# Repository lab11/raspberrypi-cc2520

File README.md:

raspberrypi-cc2520
==================

Code, hardware, and instructions to use the TI CC2520 with the Raspberry Pi.

[

](https://raw.github.com/bradjc/raspberrypi-cc2520/master/media/rpi-cc2520_2ndgen.jpg)

The CC2520 is a 802.15.4 (Zigbee) radio commonly used in low power wireless
sensor networks. Typically 802.15.4 radios are used with WSN motes and embedded
microcontrollers. A side-effect of being used in WSNs, however, is the
microcontrollers are very memory constrained. This is often a problem when
certain nodes need to keep data about a large network of nodes, for instance
routing information for all of the nodes. To remedy this we propose using a
Raspberry Pi as a mote in a WSN. This provides both ample storage (memory) and
convenient control as all the utilities in Linux are available.

Hardware
--------

I have a small PCB that fits directly on to the main header on the
RPi. It contains the CC2520, an SMA connector for an antenna, the DS2411
id chip, and three LEDs. The eagle files, gerbers and BOM can be found in the
`hardware/eagle/rpi-cc2520` folder.

Software
--------

### Kernel Module

In order to support the CC2520
you need the kernel module from https://github.com/ab500/linux-cc2520-driver.
This kernel module is designed to run on top of the Raspbian Linux distribution.

### Custom Version of Raspbian

Instead of compiling and installing the CC2520 kernel module yourself, you can
download a pre-configured
[image](http://nuclear.eecs.umich.edu/public/raspbian_cc2520_2013-09-18.zip)
of raspbian and put that on the sdcard instead.
Download the img and then install it to an SD
card ([here](http://elinux.org/RPi_Easy_SD_Card_Setup) is a helpful guide). For
reference, I use:

    dcfldd bs=4M if=raspbian_cc2520_2013-06-27.img of=/dev/sdd statusinterval=4

### TinyOS

All of the code I have for the RPi/CC2520 is based on TinyOS. You can use the
CC2520 driver without TinyOS (see the tests in the linux-cc2520-driver repo),
but for my purposes TinyOS was the best option.

To setup my workflow,
on your non-RPI computer you need a copy of the main TinyOS repository and the
tinyos folder from this repo. You also need to install the dependencies for
TinyOS. There are instructions here:
[http://docs.tinyos.net/tinywiki/index.php/Installing_TinyOS]. If you want
the simple Linux install I use, look here:
[http://energy.eecs.umich.edu/wiki/doku.php?id=tinyos_install]. The TinyOS
applications are designed to be cross compiled for the RPI.

In order for the TinyOS build system to figure out all the correct paths you
need to help it along a bit. Add the following to your `.bashrc` file:

    export TINYOS_ROOT_DIR=<path to git repo>/tinyos-main
    export TINYOS_ROOT_DIR_ADDITIONAL=<path to git repo>/raspberrypi-cc2520/tinyos:$TINYOS_ROOT_DIR_ADDITIONAL

You will also need the correct cross compiler for the RPi:
`arm-linux-gnueabi-gcc`. On Ubuntu:

    sudo apt-get install gcc-arm-linux-gnueabi

#### NesC

NesC is the first pass compiler for TinyOS. This compiler converts .nc files
into c code that gcc can handle. This code requires nesc version 1.3.5+.

#### Supported TinyOS Features

  - Gpio
  - Interrupts (high latency, can't use for timing critical operations)
  - 802.15.4 Packets
  - Active Message
  - Timers
  - DS2411
  - Busy wait
  - Command line arguments
  - Printf
  - Random numbers
  - Unix timestamps
  - Uart receive
  - TUN interface

Setup
-----

Once you have an RPi setup with Raspbian, there are various changes you may
need to make to the Raspbian install depending on what you want to do.

### Use IPv6
To use IPv6 you need to enable IPV6 on the RPI:

    $ sudo vim /etc/modules
    add ipv6 on a newline

### Enable Interface Forwarding

By default, Linux will not forward packets between interfaces. This
functionality is critical, however, if you want the RPi to act as a border
router for a  wireless network. Once interface forwarding is enabled, Linux
considers the machine to be a
router. This causes it to no longer receive IPv6 router advertisements, because
routers are typically statically configured. In most cases we'd rather not deal
with that, so we would like Linux to both accept router advertisements and to
forward packets.
To enable these you need to do
the following:

    sudo vim /etc/sysctl.conf
    uncomment the line: net.ipv6.conf.all.forwarding=1
    add the line: net.ipv6.conf.eth0.accept_ra=2

Usage
-----

Now to test the TinyOS code and the kernel module.

### Blink

Assuming you have the correct compilers, you should be able to run the following
on your desktop and have it compile successfully:

    cd tinyos-main/apps/Blink
    make rpi

To install it to the RPi you can simply do:

    make rpi install scp.<ipaddress of the rpi>

Then on the rpi:

    sudo ./BlinkAppC

Pins 7, 12, and 13 should be toggling and the LEDs on the interface board should
be blinking.

### RadioCountToLeds

To test the radio with TinyOS, run the RadioCountToLeds app on the RPi and
another mote. The basic process is the same as with the blink app above.

### Debug

If you need to, you can run the TinyOS application with GDB. To add the debug
symbols:

    make rpi debug

Then on the RPi:

    sudo gdb ./AppC

Setting Up an Actual Border Router
----------------------------------

These are the instructions for how I'm testing the RPI as a border router.
Because IPv6 support is anything but universal, this requires more manual setup
than desired.

My setup consists of using Hurricane Electric to tunnel IPv6 to the RPi and all
computers I wish to send packets to.

### Setting up the Tunnel

Go to http://www.tunnelbroker.net/ to setup a tunnel to the IP address of the
RPI. The Hurricane Electric instructions will setup an IPv6 in IPv4 tunnel
device on the RPi.

Hurricane Electric conveniently provides every tunnel it creates a /64 prefix
that they route to the end of the tunnel. This is perfect for the BorderRouter
application as the WSN nodes can use IP addresses in this range.

### Setting Up the Border Router

The RPi will be running the BorderRouter app.
The border router is required to determine the 64 bit IPv6 prefix that the
network uses. How this prefix is assigned can be handled in several ways:
IPv6 Neighbor Discovery, DHCP, or static configuration.

#### Addressing: IPv6 Neighbor Discovery

To use router solicitations and router advertisements to assign a prefix
for the network, set `BLIP_ADDR_AUTOCONF=1` in the Makefile, as well
as `BLIP_SEND_ROUTER_SOLICITATIONS=1`. This will cause the border router
to send a router solicitation in order to receive a router solicitation
and then use the prefix that it receives from the router advertisement as the
network prefix.

The next step is something must respond to the router solicitations. To do
this, setup [radvd](https://github.com/reubenhwk/radvd) to respond to router
solictitations on the interface that the border router creates. To configure
the name of the TUN device the border router creates, run the border router
app like this:

    sudo ./BorderRouterC -i tunname

#### Addressing: DHCP

Blip supports both static and dynamic IP addresses. If you wish to reduce your
burden when flashing nodes and use dynamic addresses, you need to be
running a DHCP server. Ideally you could use any router's DHCP server, but in
the likely case that isn't available, you can run a DHCP server on the RPI.

I'm using [Dibbler](http://klub.com.pl/dhcpv6/). I couldn't figure out how to
cross compile it so I downloaded it to the RPi and built it on there (yeah it
took a little while). Alternatively, you can try getting
[these directions](http://klub.com.pl/dhcpv6/doxygen/dc/dec/compilation.html#compilationCross)
for cross-compiling Dibbler to work.

    tar xf dibbler-x.x.x.tar.gz
    ./configure
    make
    sudo make install

Running Dibbler is pretty straightforward. The last key is the configuration file
located at `/etc/dibbler/server.conf`. Here is mine:

    log-colors true

    iface relay1 {
     relay tun0

     class {
      pool <ipv6/64 from Hurricane Electric>/64
     }
    }

    iface "tun0" {
     class {
      pool <ipv6/64 from Hurricane Electric>/64
     }

     client link-local fe80::212:6d52:5000:1 {
      address <ipv6/64 from Hurricane Electric>:1
      prefix <ipv6/64 from Hurricane Electric>/64
     }
    }

#### Addressing: Static

To assign a static prefix, uncomment `components StaticIPAddressC;` from `BorderRouterC.nc`
and update the prefix in `brconfig.ini`.

### Compile and Install

In `/tinyos/apps/BorderRouter`:
    
    make rpi install scp.<ip address of rpi>

### Operation

Once running the BorderRouter application will forward all IPv6 packets that are not destined
for a node in the network to the TUN interface, and then Linux can route those packets
to the Internet.

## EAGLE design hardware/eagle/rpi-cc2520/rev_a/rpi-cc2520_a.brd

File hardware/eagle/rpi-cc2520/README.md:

RPi - CC2520 Rev. A
===================

This PCB contains the TI CC2520 and Maxim DS2411 and fits directly on to P1
on the Raspberry Pi.

This design is known to be working.

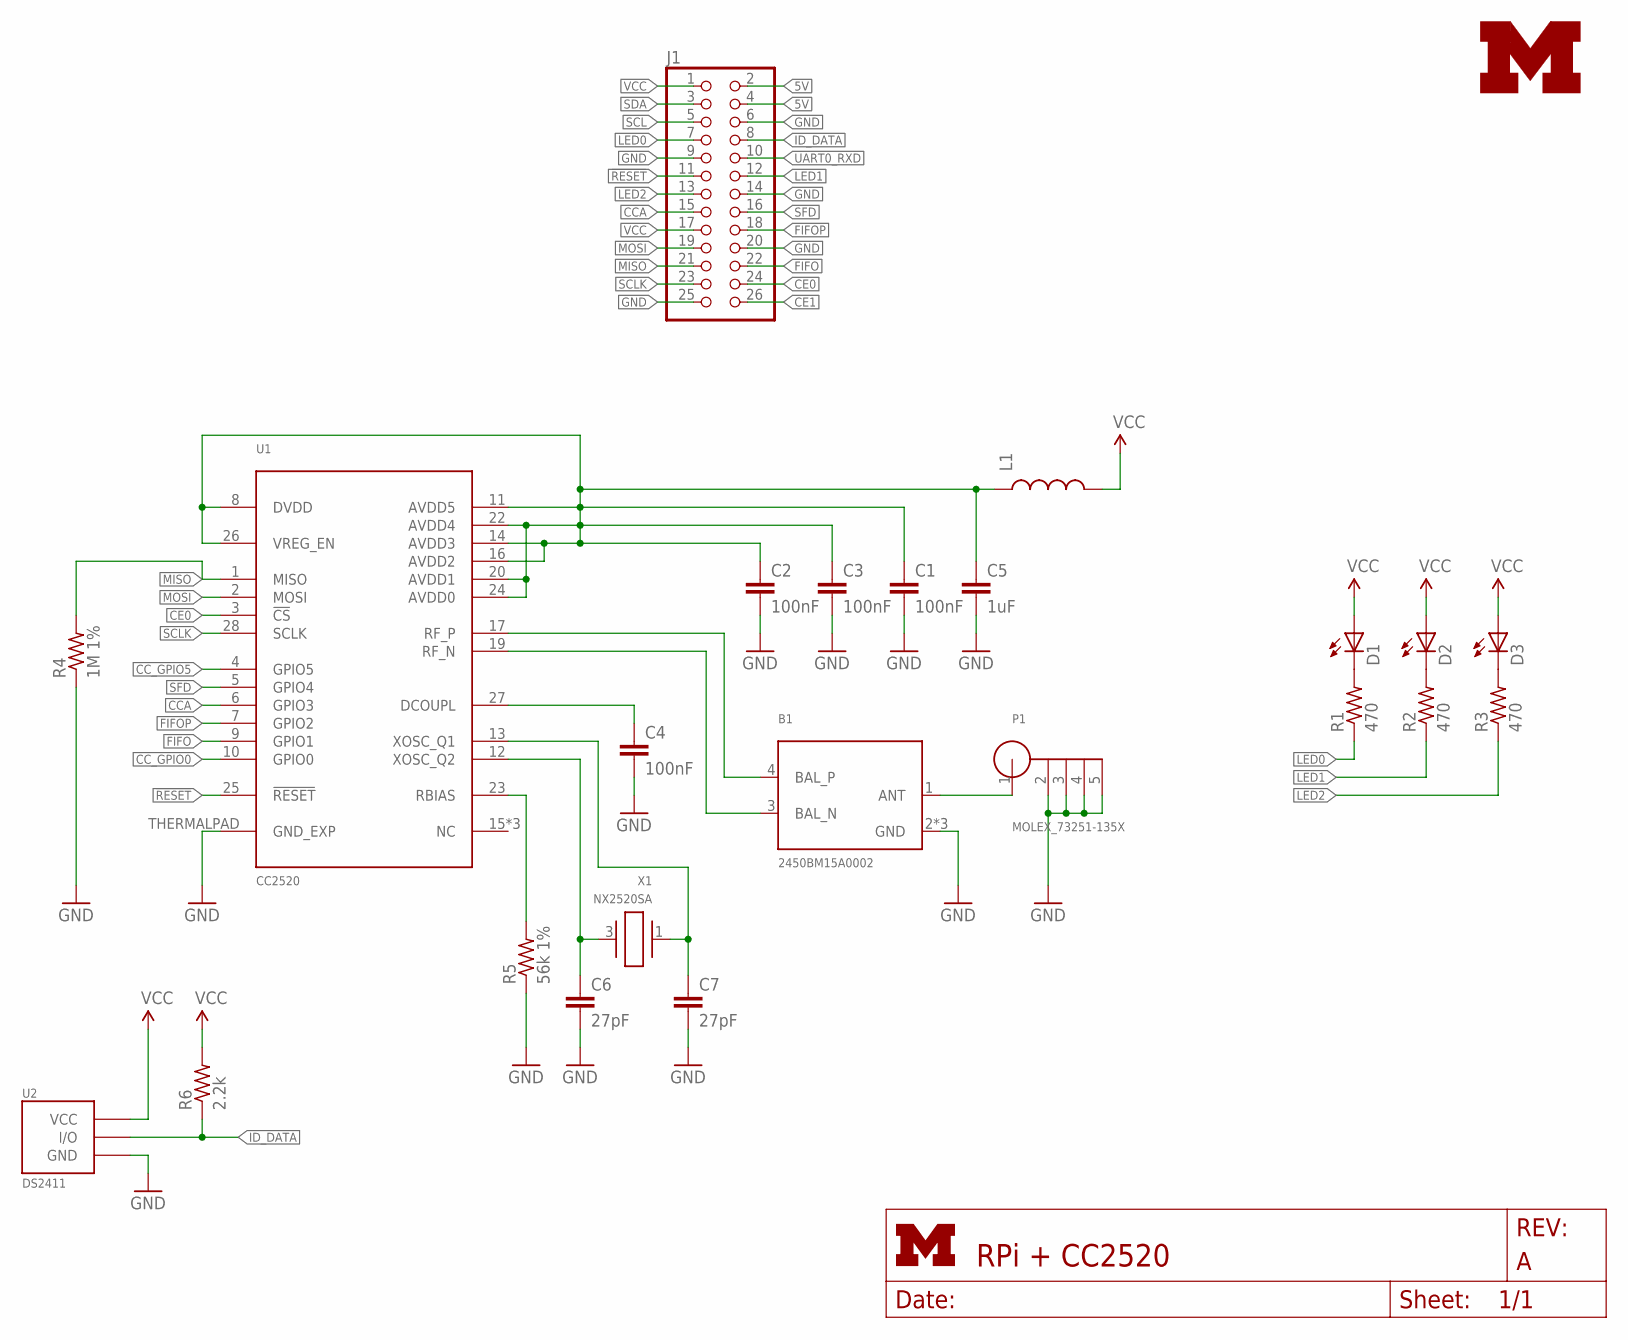
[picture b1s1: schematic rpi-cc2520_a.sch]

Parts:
B1: 2450BM15A0002; 2450BM
C1, C2, C3, C4: 100nF; C0402; DIGIKEY 490-1318-1-ND
C5: 1uF; C0603; DIGIKEY 490-1550-1-ND
C6, C7: 27pF; C0402; DIGIKEY 490-5869-1-ND
D1: LED0603; LED-0603; DIGIKEY 160-1834-1-ND
D2: LED0603; LED-0603; DIGIKEY 160-1835-1-ND
D3: LED0603; LED-0603; DIGIKEY 160-1837-1-ND
J1: PINHD-2X13; 2X13; DIGIKEY SAM1204-13-ND
L1: INDUCTOR0603; 0603; DIGIKEY 490-1015-1-ND
P1: MOLEX_73251-135X; SMA-J/PCB
R1, R2, R3: 470; R0402; DIGIKEY RHM470JCT-ND
R4: 1M 1%; R0402; DIGIKEY RHM1.00MCDCT-ND
R5: 56k 1%; R0402; DIGIKEY P56.0KLCT-ND
R6: 2.2k; R0402; DIGIKEY RHM2.2KCECT-ND
U1: CC2520; S-PVQFN-N28
U2: DS2411; SOT-23
U$1: UMICH_SOLID_SMALL; UMICH_SOLID_75MIL
X1: NX2520SA

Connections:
5V: J1.2, J1.4
!RESET: J1.11, U1.25 (!RESET)
CCA: J1.15, U1.6 (GPIO3)
CC_GPIO0: U1.10 (GPIO0)
CC_GPIO5: U1.4 (GPIO5)
CE0: J1.24, U1.3 (!CS)
CE1: J1.26
FIFO: J1.22, U1.9 (GPIO1)
FIFOP: J1.18, U1.7 (GPIO2)
GND: B1.2 (GND), B1.5 (GND), B1.6 (GND), C1.2, C2.2, C3.2, C4.2, C5.2, C6.2, C7.2, J1.6, J1.9, J1.14, J1.20, J1.25, P1.2, P1.3, P1.4, P1.5, R4.1, R5.1, U1.THERMALPAD (GND_EXP), U2.3 (GND)
ID_DATA: J1.8, R6.1, U2.1 (I/O)
LED0: J1.7, R1.1
LED1: J1.12, R2.1
LED2: J1.13, R3.1
MISO: J1.21, R4.2, U1.1 (MISO)
MOSI: J1.19, U1.2 (MOSI)
unnamed: D1.C, R1.2
unnamed: D2.C, R2.2
unnamed: D3.C, R3.2
unnamed: C1.1, C2.1, C3.1, C5.1, L1.1, U1.8 (DVDD), U1.11 (AVDD5), U1.14 (AVDD3), U1.16 (AVDD2), U1.20 (AVDD1), U1.22 (AVDD4), U1.24 (AVDD0), U1.26 (VREG_EN)
unnamed: B1.1 (ANT), P1.1
unnamed: C7.1, U1.13 (XOSC_Q1), X1.1
unnamed: C4.1, U1.27 (DCOUPL)
unnamed: C6.1, U1.12 (XOSC_Q2), X1.3 (2)
unnamed: R5.2, U1.23 (RBIAS)
RF_N: B1.3 (BAL_N), U1.19 (RF_N)
RF_P: B1.4 (BAL_P), U1.17 (RF_P)
SCL: J1.5
SCLK: J1.23, U1.28 (SCLK)
SDA: J1.3
SFD: J1.16, U1.5 (GPIO4)
UART0_RXD: J1.10
VCC: D1.A, D2.A, D3.A, J1.1, J1.17, L1.2, R6.2, U2.2 (VCC)

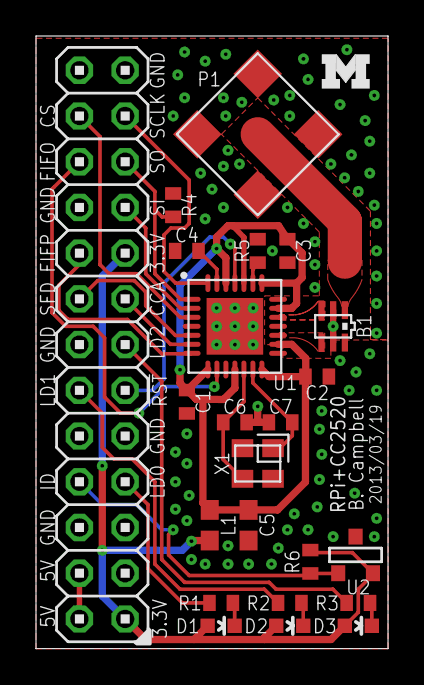
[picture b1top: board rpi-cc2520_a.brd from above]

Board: 2 copper layers, 19.6 x 34.0 mm, 24 parts (0 on the bottom side), 27 nets.

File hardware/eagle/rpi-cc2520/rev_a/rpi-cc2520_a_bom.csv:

# Bill of Materials
# Converted from rpi-cc2520_a_bom.xls
# Generated by bom_to_text.py

Qty,Value,Device,Package,Parts,Description,DIGIKEY,DIGIREEL
1,,2450BM15A0002,2450BM,B1,BALUN JTI MATCHED ZIGBEE,712-1536-1-ND,712-1536-6-ND
4,100nF,C-EUC0402,C0402,"C1, C2, C3, C4","CAPACITOR, European symbol",490-1318-1-ND,490-1318-6-ND
1,1uF,C-EUC0603,C0603,C5,"CAPACITOR, European symbol",490-1550-1-ND,490-1550-6-ND
2,27pF,C-EUC0402,C0402,"C6, C7","CAPACITOR, European symbol",490-5869-1-ND,490-5869-6-ND
1,,LED0603,LED-0603,D1,Green LED,160-1834-1-ND,160-1834-6-ND
1,,LED0603,LED-0603,D2,Red LED,160-1835-1-ND,160-1835-6-ND
1,,LED0603,LED-0603,D3,Blue LED,160-1837-1-ND,160-1837-6-ND
1,,PINHD-2X13,2X13,J1,PIN HEADER,SAM1204-13-ND,SAM1204-13-ND
1,,INDUCTOR0603,L0603,L1,Inductors,490-1015-1-ND,490-1015-6-ND
1,,MOLEX_73251-135X,SMA-J/PCB,P1,SMA JACK SMT 50 OHM,WM9357-ND,WM9357-ND
3,470,R-US_R0603,R0402,"R1, R2, R3","RESISTOR, American symbol",RHM470JCT-ND,RHM470JTR-ND
1,1M 1%,R-US_R0402,R0402,R4,"RESISTOR, American symbol",RHM1.00MCDCT-ND,RHM1.00MCDDKR-ND
1,56k 1%,R-US_R0402,R0402,R5,"RESISTOR, American symbol",P56.0KLCT-ND,P56.0KLDKR-ND
1,2.2k,R-US_R0402,R0402,R6,"RESISTOR, American symbol",RHM2.2KCECT-ND,RHM2.2KCEDKR-ND
1,,CC2520,S-PVQFN-N28,U1,2.4 GHZ IEEE 802.15.4/ZIGBEE® RF TRANSCEIVER,296-22996-1-ND,296-22996-6-ND
1,,DS2411,SOT-23,U2,IC SILICON SERIAL NUMBER SOT-23,DS2411R+CT-ND,DS2411R+DKR-ND
1,,NX2520SA,NX2520SA,X1,CRYSTAL 32MHZ 10PF SMD,644-1065-1-ND,644-1065-6-ND
1,,ANTENNA,,,ANTENNA 2.45GHZ 1/4 WAVE SMA,ANT-2.4-CW-RH-SMA-ND,ANT-2.4-CW-RH-SMA-ND

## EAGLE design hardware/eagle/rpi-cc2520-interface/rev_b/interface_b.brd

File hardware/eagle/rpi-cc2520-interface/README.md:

RPi - CC2520 Interface
======================

This board bridges the RPi and the TI CC2520EM evaluation module.

Revision B is known to be working, but requires an expensive EVM. A newer
design can be found in the rpi-cc2520 folder.

Rev B
-----

- Wired the radio GPIO lines directly on the PCB.
- Added LEDs.

Rev A
-----

- Fits the CC2520EM. Requires jumper wires between the radio GPIOs and the RPi
GPIOs.

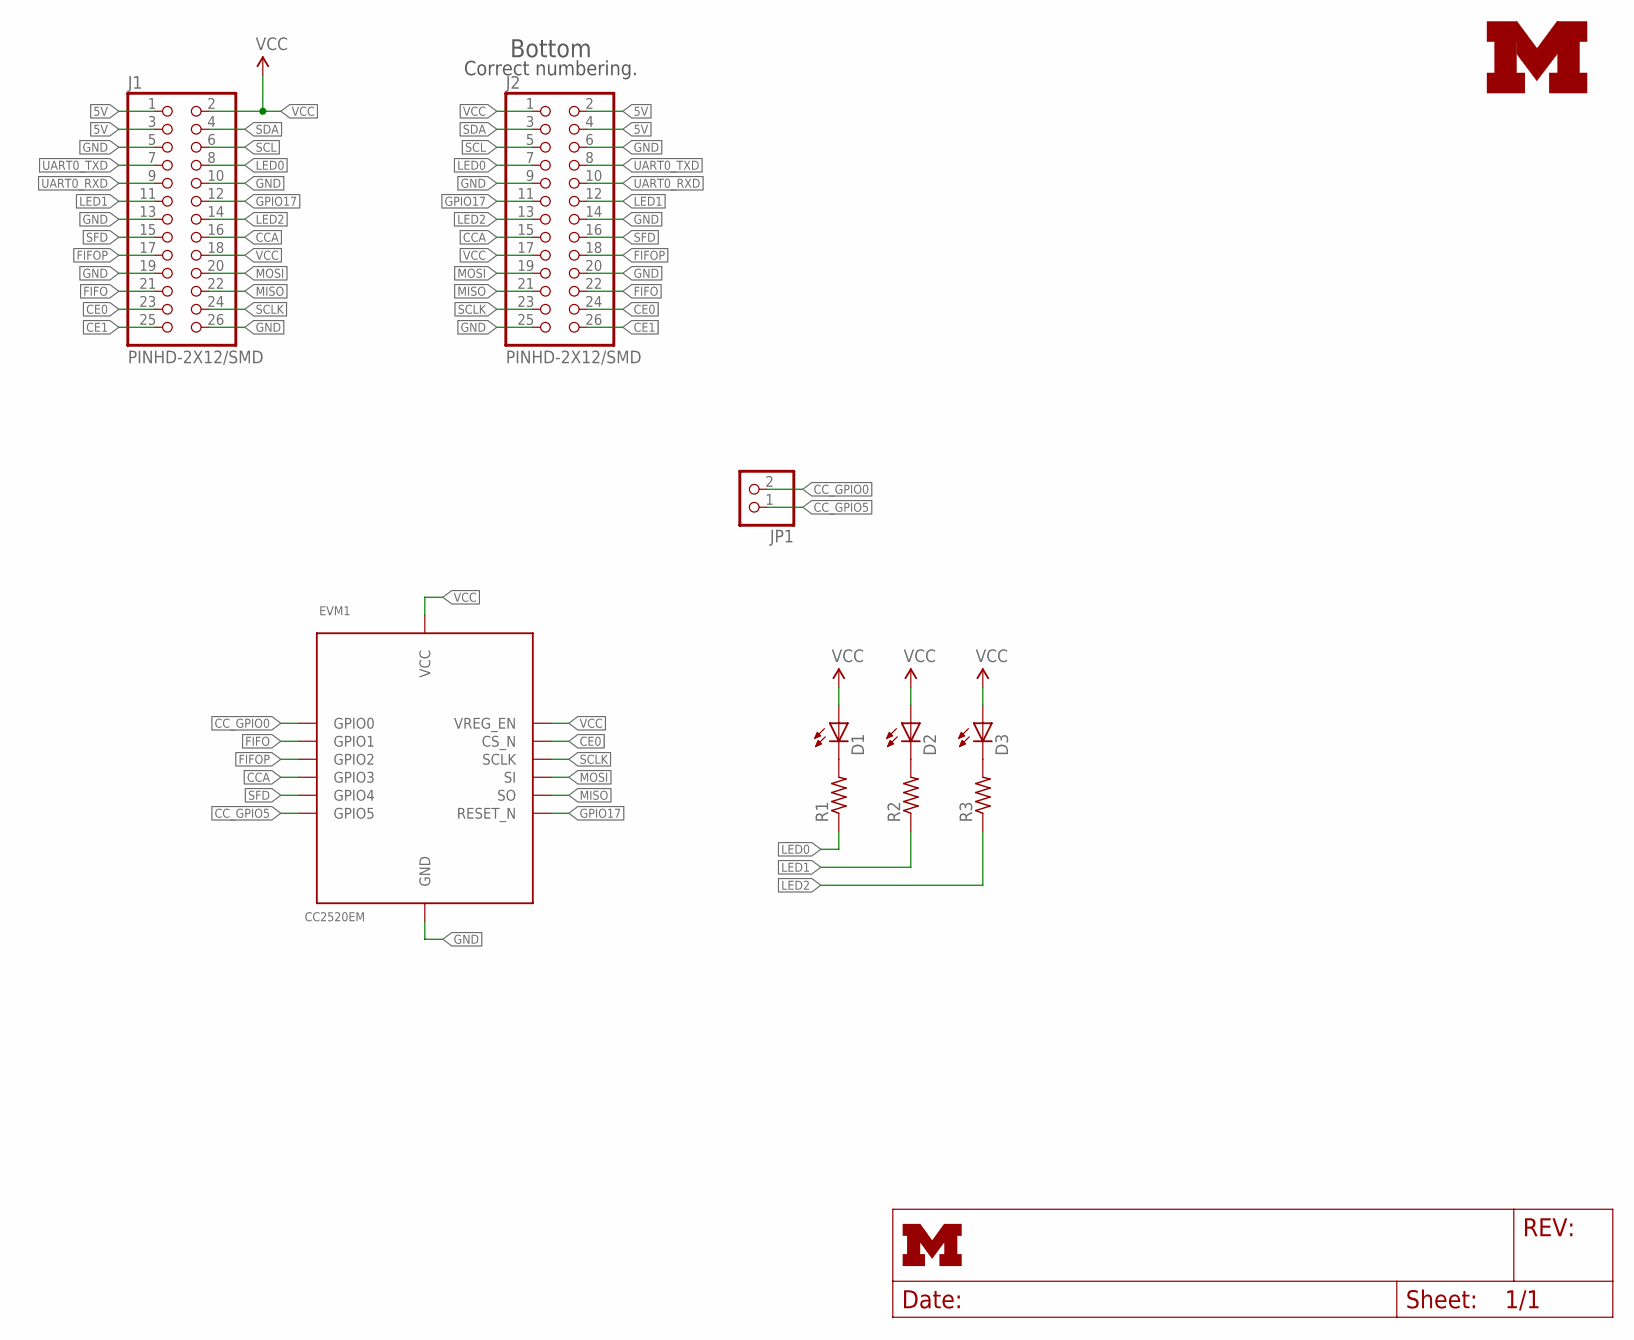
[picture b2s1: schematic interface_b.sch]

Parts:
D1, D2, D3: LED0603; LED-0603
EVM1: CC2520EM; TI_CC_EVM
J1, J2: PINHD-2X12/SMD; 2X13/SMD
JP1: PINHD-1X2; 1X02
R1, R2, R3: R-US_R0603; R0603
U$1: UMICH_SOLID_SMALL; UMICH_SOLID_75MIL

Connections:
5V: J1.1, J1.3, J2.2, J2.4
CCA: EVM1.P1_12 (GPIO3), J1.16, J2.15
CC_GPIO0: EVM1.P1_3 (GPIO0), JP1.2
CC_GPIO5: EVM1.P2_19 (GPIO5), JP1.1
CE0: EVM1.P1_14 (CS_N), J1.23, J2.24
CE1: J1.25, J2.26
FIFO: EVM1.P1_7 (GPIO1), J1.21, J2.22
FIFOP: EVM1.P1_9 (GPIO2), J1.17, J2.18
GND: EVM1.P1_1 (GND), EVM1.P1_19 (GND), J1.5, J1.10, J1.13, J1.19, J1.26, J2.6, J2.9, J2.14, J2.20, J2.25
GPIO17: EVM1.P2_15 (RESET_N), J1.12, J2.11
LED0: J1.8, J2.7, R1.1
LED1: J1.11, J2.12, R2.1
LED2: J1.14, J2.13, R3.1
MISO: EVM1.P1_20 (SO), J1.22, J2.21
MOSI: EVM1.P1_18 (SI), J1.20, J2.19
unnamed: D1.C, R1.2
unnamed: D2.C, R2.2
unnamed: D3.C, R3.2
SCL: J1.6, J2.5
SCLK: EVM1.P1_16 (SCLK), J1.24, J2.23
SDA: J1.4, J2.3
SFD: EVM1.P2_18 (GPIO4), J1.15, J2.16
UART0_RXD: J1.9, J2.10
UART0_TXD: J1.7, J2.8
VCC: D1.A, D2.A, D3.A, EVM1.P1_10 (VREG_EN), EVM1.P2_7 (VCC), EVM1.P2_9 (VCC), J1.2, J1.18, J2.1, J2.17

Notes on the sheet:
Bottom
Correct numbering.

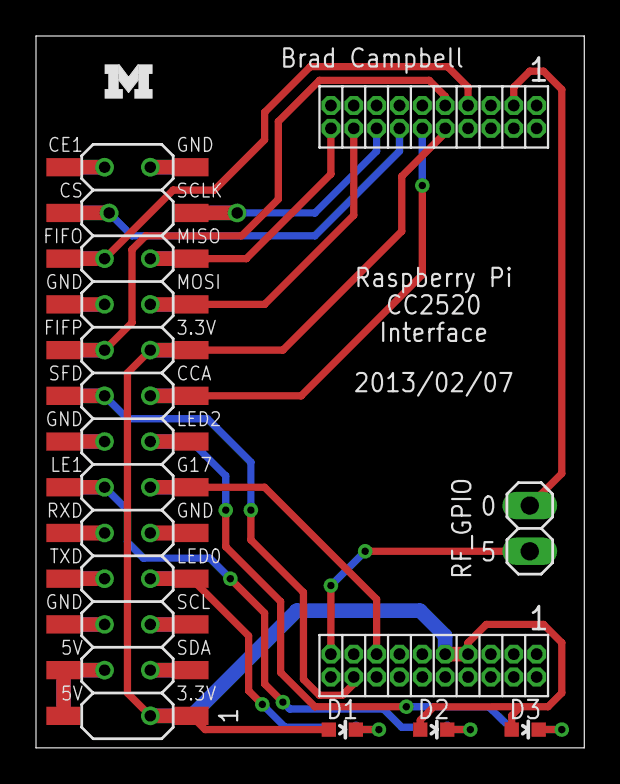
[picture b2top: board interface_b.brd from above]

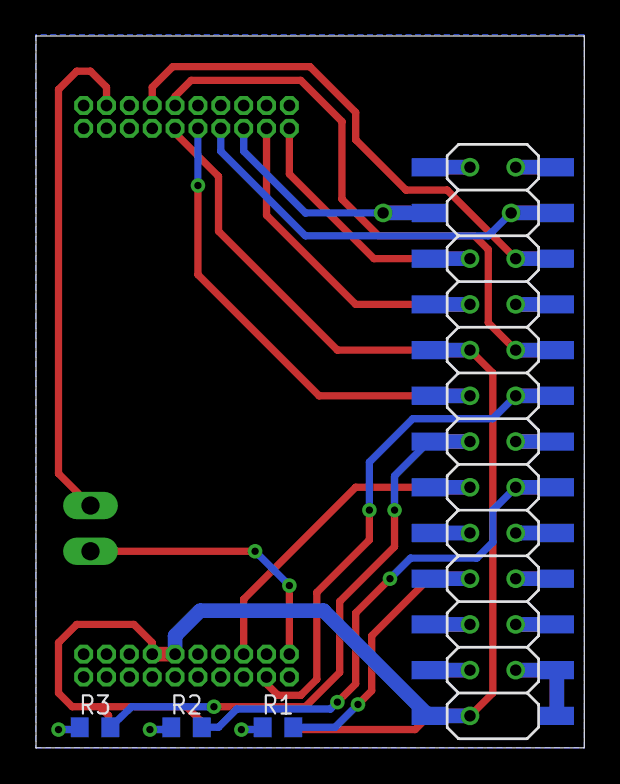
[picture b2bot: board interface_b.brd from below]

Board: 2 copper layers, 30.5 x 39.5 mm, 11 parts (4 on the bottom side), 25 nets.

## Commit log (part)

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2013-01-20 added function bodies to RadioBareP
    Also moved split control into radiobarep, i can't remember what my
    rationale was for making it its own file...
2013-01-20 adding a start at a python udp client
    I'm not sure if it doesn't work or if I'm making bad assumptions about
    how packets move in linux.
2013-01-20 renamed driver to drop bare
2013-01-20 updated the am cc2520rpi driver to compile
    NOTE: This doesn't seem to work. I believe it is segfaulting because of
    the same reason I always have trouble. Multiple things are wired to
    CC2520RpiSendC and sendDone triggers multiple things and that makes bad
    things happen.
2013-01-20 Fixed bug with AM stack
    No longer wire to CC2520RpiRadioC, rather we use CC2520RpiRadioP. This
    keeps the other, non AM, stack from being wired up. Then the segfault
    goes away. Although I can't explain the need for the signalWrapper.h
    file.
2013-01-20 fixing up some default values.
    The ACK timeout value was measured using the RadioToBlink test app
    to be optimally around 2.5ms. I think I might be measuring it slightly
    differently than the Soft-ACK rfxlink layer. I like my way better at
    the moment and it's not super important to be consistent here.
    I think our 2.5ms is approximately equal to the CC2420 stack's
    800uS.
2013-01-20 Added new atomic section code.
    We now use a mutex to ensure the atomicity of all TinyOS atomic sections.
    Of note is how we handle recursive locking. In traditional TinyOS
    enable/disable interrupt code it would return a 1 or 0 indicating whether
    interrupts were enabled or disabled. This was okay because of the nature
    of the way interrupts execute ensured that they would always run to
    completion.
2013-01-20 Refactoring of the receive code to be more performant.
    We now use a condition variable and run the receive event
    on the main thread. The pending boolean is set to TRUE when
    a packet is pending the completion of the receive event. This
    effectively allows for the receive thread to continue and wait
    for another packet.
    We post a task to the TinyOS scheduler which will cause it to run
2013-01-20 Added simple send to mote to the border router.
    Just for testing purposes.
2013-01-21 changed ip addresses
2013-01-21 Edited test apps
2013-01-21 Better handling the return value from write()
2013-01-21 added improved address info
2013-01-21 changed command for tun0 settings
2013-01-21 Better handling of extended addressing.
    Both the RadioP config init and the blip extended address pull from
    LocalIeeeEui64C now.
    Having problems using extended addresses other than 0x00000...001,
    however. Need a test for the driver directly.
2013-01-21 Better handling of return info from packet receive
    I believe the two bytes that follow each packet from the read() call are
    now parsed and saved correctly.
    I added a ack struct to the metadata info because that seemed like the
    cleanest way to keep track of whether an ack was received. Putting it in
    the cc2520_metadata_t struct would violate the assumed conditions of the
    cast in ReciveP (the ack field wouldn't point to meaningful data there).
2013-01-21 Quick cleaning pass over the cc2520rpi code
2013-01-22 Overiding the blip UDP to add IPForward
    At some point in BLIP all packets destined for the border router that
    don't match any bound to ports in the tinyos app have to go to linux for
    further routing. The best place with minimal need to override BLIP that
    I found was to do it on each of the transport layer modules. So far I've
    only done UDP where before the function just returned if the port was
    not bound. Now it dumps to TunC.
2013-01-22 Better print
2013-01-22 Moved where the seq no is set
    Sequence number is now set above the link layer.
2013-01-23 testing dhcp server
2013-01-26 Fixed up the Tun driver to use a similar task post
    Now it uses a safer mechanism to post the received
    TUN packets.
    TODO: Actually create the right data struct to call
    sendDone.
2013-01-28 Added #define to remove printfs
    Can now selectively decide to debug radio with printfs
    Conflicts:
    tinyos/tos/chips/cc2520rpi/CC2520RpiReceiveP.nc
    tinyos/tos/chips/cc2520rpi/CC2520RpiSendP.nc
2013-01-28 better debug printing for tun
2013-01-28 Added threadwait to tunP
2013-01-29 very rough code to extract ipv6 pkt from ipv4
    Just want to commit this for posterity in case I want to see my work.
2013-01-30 Enabled waiting on cond variable
    es starting
2013-01-30 Working on deadlock issue
2013-01-31 Better send printf debug as well
2013-01-31 Fixed atomic errors
2013-01-31 fixing compiler warnings
2013-01-31 added route to tun device
    Makes DHCP unicast work. Needed to use stock blip.
2013-02-07 Updated README with new instructions
    Improved the DHCP section
2013-02-08 really quick update to readme
2013-02-08 cleaning up some old code
2013-02-13 update gitignore to remove eagle
2013-02-13 Cleaned spaces
2013-02-14 Update how file desc. are handled
2013-02-14 Send and Receive updated to select
    Send uses 2 pipes: one to send data from the app to the driver and one
    to send the rssi from the driver to the app.
2013-02-14 readding iofile
2013-02-14 updated gitignore to hide gerbmerge extras
2013-02-16 removing old blip changes
    No longer needed, or are being merged into tinyos-main
2013-02-16 changed buffer size
2013-02-16 Added debug_printf.h
2013-02-19 binds on all interfaces
2013-02-19 Actually check if the crc failed
2013-02-23 updated to reflect platform name change
2013-02-23 Updated to v2 macros and renamed
2013-02-25 Have forked children rename themselves
    (untested as Brad's changes are so disperse and undocumented it
    makes things impossible to test)
2013-02-25 Updated with info about getting tinyosmain changes
2013-02-25 child processes now die when parent does
2013-03-06 Setting radio channel for cc2520 as well
2013-03-07 Adding module to make it easy to query for time
    Adds nice interface for unix timestamps.
2013-03-11 Updated Ieee154Bare interface
    Now matches the changes I made to tinyos-main.
    Removes metadata stuff from Ieee154BareC. It shouldn't be in there.
2013-03-11 adding the new board version
    This board will be a standalone pcb with the cc2520 directly on it, no
    $100 eval board needed.
2013-03-12 adding cc2520 and related parts
2013-03-12 adding datasheets
2013-03-12 added bom for old board rev b
2013-03-12 added balun to library
2013-03-12 getting the polygons right
2013-03-13 Updated bom with new labels
2013-03-13 zipped up all the ti cc2520em documentation
2013-03-13 added balun
2013-03-13 updated rf traces and silkscreen labels
2013-03-14 cleaning up antenna trace with nice roundedness
2013-03-20 committing gerbers
    I sent rev a to be built
2013-03-20 Created Hpl file for ds2411 chip.
    This wires to the gpio pin.
2013-03-20 Added new directories to nesc search path
2013-03-20 compiles now - fixed some interface names
2013-03-20 update path for tun folder move
2013-03-24 Better busywait that doesn't give up the cpu
    Using nanosleep() was not very accurate.
2013-03-24 Updated the ds2411 chip
    Added comments
    Fixed byte order
2013-03-24 Removed the ds2411 stuff from this repo
    It is now in my tinyos-main repo (ds2411 branch) and hopefully will get
    merged into the real tinyos-main.
2013-03-25 Fixed missing return value
    This prevents the thing from segfaulting
2013-03-25 added more error checking
2013-03-26 printing at each send
2013-03-27 adding images of rpi-cc2520
2013-03-27 Added signal handler on sigint
    Turns off the leds before exiting.
2013-03-28 fixed _start problem, improved build system
    Added debug flag which compiles with -g
2013-03-28 Added support for LPL flags
2013-03-29 cleaned up, fixed pipe error and int ret
2013-03-29 adding simple uart test app
2013-03-29 moved uart test to better name
2013-03-29 added test app for new uart driver
2013-03-29 tweaks to get UartBB closer
    I will proably just give up on this driver as it is toooo slow
2013-04-01 readme to note what pins need to be jumpered
2013-04-01 Added all of the other interrupt pins
    Nice parametrized interface so I don't have a million doubled functions.
2013-04-01 moved pdfs to their own folder
2013-04-01 added timestamp, fixed bug
    No longer returns a single newline packet from uart
2013-04-05 Adding support for random numbers
    I realize now that the naming of this is bad.
    I will fix it in the future.
2013-04-10 spacing
2013-04-12 moved interface to interfaces folder
2013-04-12 Changed name of random
    Now reflects that it uses linux's random source.
    You need to explicitly wire to RadomLinuxC to use it.
2013-04-12 added comment
2013-04-12 Added more module specific debug prints
2013-04-12 don't need old timer interfaces
2013-04-12 bit bang uart doesn't work
2013-04-12 removing test for code that no longer exists
2013-04-12 added notes about the hardware
2013-04-15 Updated radio debug ioctl
2013-04-20 working on the uart module
    Adding a couple options.
2013-04-20 Added P5 gpio pins
2013-04-21 compile bug
2013-04-21 not sure if I added to this
2013-06-03 Compatible with make-no-environ
    Updated the make system to work with my make-no-environ branch.
2013-06-19 removed signalWrapper
    Bug fix for nesc removes the need for the workaround.
    Fixes issue #7
2013-06-28 edited readme
2013-06-28 Updated to current version of ds2411 branch
2013-06-28 Full git command
2013-07-05 Added better printf to persistent tcp
2013-07-15 Added blip quick packet test
    This is to make blip be able to send a packet instantly.
2013-07-16 Added simple app to dump received packets.
2013-07-18 blip quick packet chagnes
2013-07-19 added way to configure the prefix
2013-07-20 changed how cc2520 rpi instal work
2013-07-22 Set interface route
2013-08-05 Small fixes to printf and make
2013-08-19 updated RCTLBlip to work with new make system
2013-08-19 removed old reference to pthreads
2013-08-28 cleaned up bare receive
2013-08-28 fixed tos length bug
2013-09-21 new version of raspbian
2013-10-21 changed to um eui64
2013-10-23 tunnel is coming along
2013-10-24 server works
    its probably buggy but there is a hacked together version that works
2013-10-24 channel
2013-10-24 added Tup buildsystem
2013-10-25 things are working BOOM
2013-10-25 started prefixes.data
2013-10-25 added readme for tunnel
2013-10-25 Added scripts to make it run on boot
2013-11-02 fixed an issue with break
    I was not breaking out of the correct loop.
    Also added some better error handling.
2013-11-03 script that posts rpi ip to server
2013-11-26 Readme is updated to say what it is
2013-12-11 minor updates to ipv6 tunnel
2014-01-09 cc2520 pcb documentation
2014-01-10 updated rpi info file
2014-01-20 reconnect in client changed
2014-02-24 updated TUN
    1. No longer uses brconfig.ini. Now uses whatever the set address is at
    runtime to configure the tun interface.
    2. Can now change the TUN device name. TunP calls TunName to get the
    name of the TUN, which can be changed in a app specific manner.
2014-02-24 border router uses brconfig.ini to set its ip
2014-02-26 tun interface sets ll address again
2014-02-26 tun device use ioctl rather than ssystem
2014-03-05 cleaned up addressing in border router
2014-03-19 added border router run script
    runs all the things on the border router
2014-03-19 better fix to linux networking in readme
2014-03-20 ipv6 tunnel: client better reconnects
2014-03-20 fixed deadlock issue
2014-03-20 Pick a compiler that has linux support...
2014-03-27 update uart to set RX gpio to alternate
2014-03-29 fixing mixed spaces/tabs
2014-09-22 removed static ip from border router
2014-09-22 add channel variable for barereceive makefile
2014-10-13 make-no-environ was merged to tinyos-master
    no need for special instructions
2014-10-23 added app that sniffs packets
2014-12-14 rpi -> generic arm linux
2014-12-14 creating a gap platform
2014-12-21 makefile for other border router
2014-12-23 prevent loops from packets in-out of this network
2014-12-23 fix comment
2014-12-24 rcombine comment
2015-04-01 supporting not just rpi
2015-04-01 need dummy file for bbb compile

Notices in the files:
parts and their libraries:
SparkFun-LED: Licensing: CC v3.0 Share-Alike You are welcome to use this library for commercial purposes.
